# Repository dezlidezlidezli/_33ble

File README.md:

# _33BLE
A bluetooth drop-in PCB for the [_33 keyboard](https://github.com/tominabox1/_33-Keyboard) by [tominabox1](https://github.com/tominabox1). Documentation is available [here](https://dez.li/_33ble), and the ZMK config repository is available [here](https://github.com/dezlidezlidezli/underscore33-zmk-config). 

The board can be produced at [JLCPCB](jlcpcb.com) for rather cheap, and through their PCBA service they will assemble every component other than the the [Holyiot 18010 module](https://www.aliexpress.com/item/32868002366.html). You'll need to purchase this seperately, and solder it. Files for this can be found in the Production Files directory, when ordering make sure to choose "assemble bottom side" and tooling holes aded by JLCPCB. 

You'll also need to flash the bootloader to the Holyiot module. The bootloader file can be found [here](/underscore33_bootloader.hex), and should be flashed using an ST-Link V2 clone, or a J-Link. Details for how to do this are available on the nice!keyboards wiki, and on the nRFMicro wiki. Please note that the Holyiot module does not need to be unlocked. 

Alternatively, you can choose to export files suited for another manufacturer, such as Elecrow or PCBWay, where they will assemble the entire board. Some manufacturers may also be able to flash the bootloader in their factory, so this may be worth asking your customer support representative. 

Thank you to [Makenova](https://github.com/makenova) and [Matthew Dias](https://github.com/matthewdias) for funding the open-sourcing of this project.

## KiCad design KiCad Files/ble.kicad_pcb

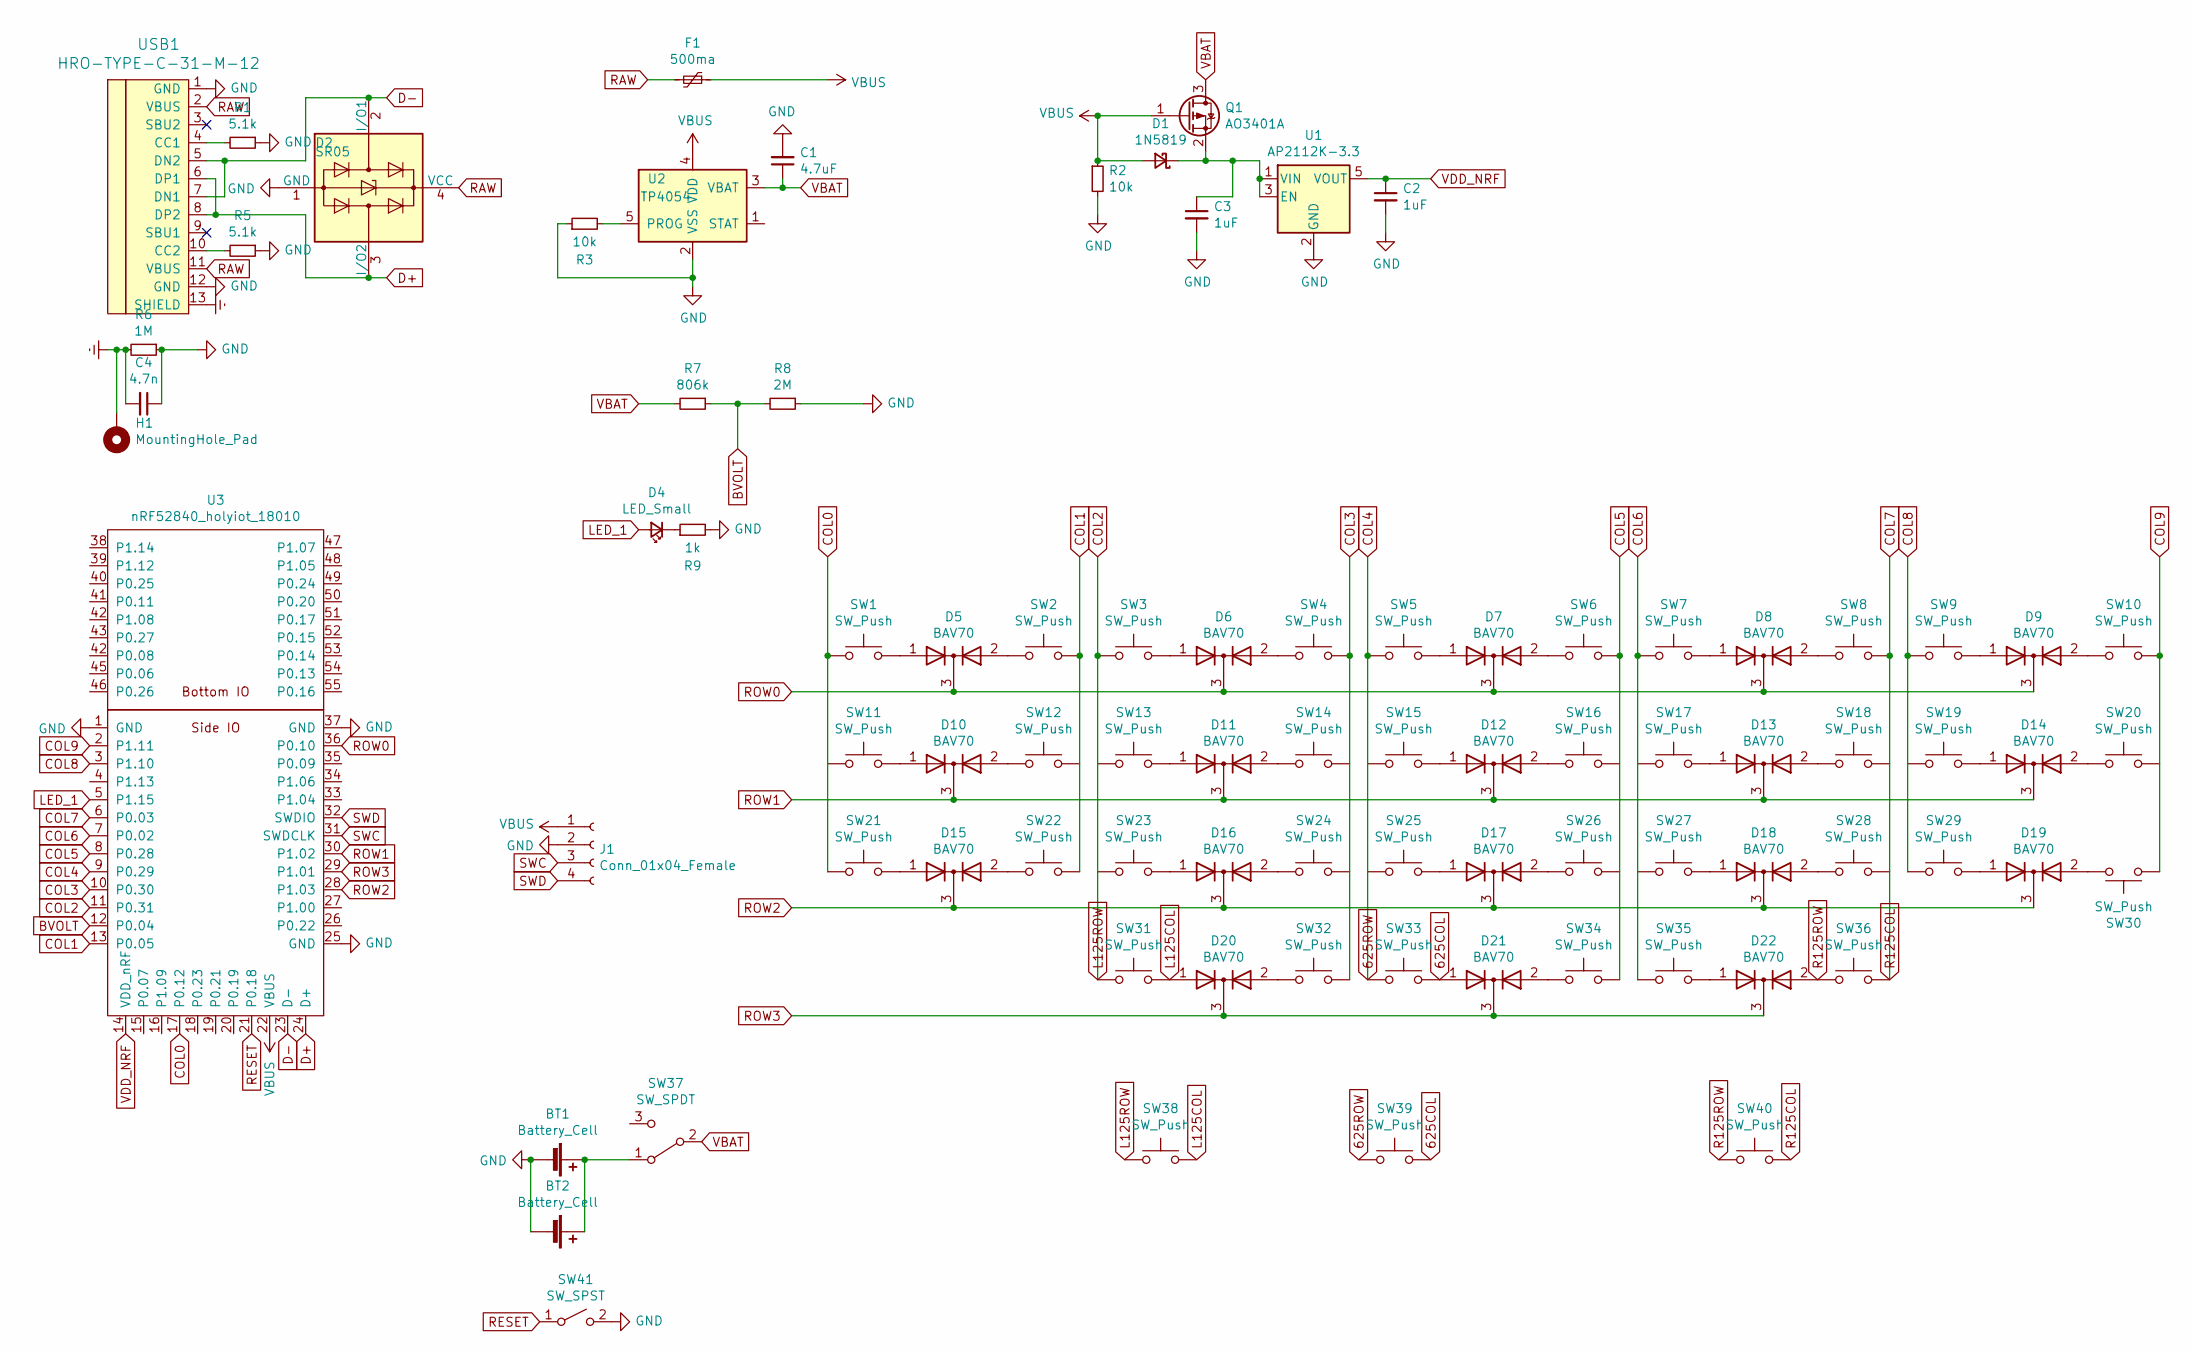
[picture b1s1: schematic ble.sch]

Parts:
BT1: Battery_Cell; JST_PH_S2B-PH-K_1x02_P2.00mm_Horizontal
BT2: Battery_Cell; custombatteryconnector
C1: 4.7uF; C_0805_2012Metric
C2, C3: 1uF; C_0805_2012Metric
C4: 4.7n; C_0805_2012Metric
D1: 1N5819; D_SOD-123
D2: SR05; SOT-143
D4: LED_Small; D_0805_2012Metric
D5, D6, D7, D8, D9, D10, D11, D12, D13, D14, D15, D16, D17, D18, D19, D20, D21, D22: BAV70; SOT-23
F1: 500ma; Fuse_1206_3216Metric
H1: MountingHole_Pad
J1: Conn_01x04_Female; PinSocket_1x04_P2.54mm_Vertical
Q1: AO3401A; SOT-23
R1, R5: 5.1k; R_0805_2012Metric
R2, R3: 10k; R_0805_2012Metric
R6: 1M; R_0805_2012Metric
R7: 806k; R_0805_2012Metric
R8: 2M; R_0805_2012Metric
R9: 1k; R_0805_2012Metric
SW1, SW2, SW3, SW4, SW5, SW6, SW7, SW8, SW9, SW10, SW11, SW12, SW13, SW14, SW15, SW16, SW17, SW18, SW19, SW20, SW21, SW22, SW23, SW24, SW25, SW26, SW27, SW28, SW29, SW30, SW31, SW36: SW_Push; MXOnly-1U-NoLED
SW32, SW35, SW38, SW40: SW_Push; MXOnly-1.25U-NoLED
SW33: SW_Push; MXOnly-2.25U-ReversedStabilizers-NoLED
SW34: SW_Push; MXOnly-2U-ReversedStabilizers-NoLED
SW37: SW_SPDT; SW_SPDT_PCM12
SW39: SW_Push; MXOnly-6.25U-ReversedStabilizers-NoLED
SW41: SW_SPST; SW_SPST_TL3342
U1: AP2112K-3.3; SOT-23-5
U2: TP4054; SOT-23-5
U3: nRF52840_holyiot_18010
USB1: HRO-TYPE-C-31-M-12; HRO-TYPE-C-31-M-12-HandSoldering

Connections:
625COL: D21.1 (A), SW33.2, SW39.2
625ROW: SW5.1, SW15.1, SW25.1, SW33.1, SW39.1, U3.9 (P0.29)
BVOLT: R7.1, R8.2, U3.12 (P0.04)
COL0: SW1.1, SW11.1, SW21.1, U3.17 (P0.12)
COL1: SW2.2, SW12.2, SW22.2, U3.13 (P0.05)
COL2: SW3.1, SW13.1, SW23.1, SW31.1, SW38.1, U3.11 (P0.31)
COL3: SW4.2, SW14.2, SW24.2, SW32.2, U3.10 (P0.30)
COL5: SW6.2, SW16.2, SW26.2, SW34.2, U3.8 (P0.28)
COL6: SW7.1, SW17.1, SW27.1, SW35.1, U3.7 (P0.02)
COL7: SW8.2, SW18.2, SW28.2, SW36.2, SW40.2, U3.6 (P0.03)
COL8: SW9.1, SW19.1, SW29.1, U3.3 (P1.10)
COL9: SW10.2, SW20.2, SW30.1, U3.2 (P1.11)
D+: D2.3 (I/O2), U3.24 (D+), USB1.6 (DP1), USB1.8 (DP2)
D-: D2.2 (I/O1), U3.23 (D-), USB1.5 (DN2), USB1.7 (DN1)
Earth: C4.2, H1.1, R6.2, USB1.13 (SHIELD)
GND: BT1.2 (-), BT2.2 (-), C1.2, C2.2, C3.2, C4.1, D2.1 (GND), J1.2, R1.1, R2.2, R3.1, R5.1, R6.1, R8.1, R9.2, SW41.2 (B), U1.2 (GND), U2.2 (VSS), U3.1 (GND), U3.25 (GND), U3.37 (GND), USB1.1 (GND), USB1.12 (GND)
L125COL: D20.1 (A), SW31.2, SW38.2
LED_1: D4.2 (A), U3.5 (P1.15)
unnamed: BT1.1 (+), BT2.1 (+), SW37.1 (A)
unnamed: C3.1, D1.1 (K), Q1.2 (S), U1.1 (VIN), U1.3 (EN)
unnamed: D4.1 (K), R9.1
unnamed: D5.1 (A), SW1.2
unnamed: D5.2 (A), SW2.1
unnamed: D6.1 (A), SW3.2
unnamed: D6.2 (A), SW4.1
unnamed: D7.1 (A), SW5.2
unnamed: D7.2 (A), SW6.1
unnamed: D8.1 (A), SW7.2
unnamed: D8.2 (A), SW8.1
unnamed: D9.1 (A), SW9.2
unnamed: D9.2 (A), SW10.1
unnamed: D10.1 (A), SW11.2
unnamed: D10.2 (A), SW12.1
unnamed: D11.1 (A), SW13.2
unnamed: D11.2 (A), SW14.1
unnamed: D12.1 (A), SW15.2
unnamed: D12.2 (A), SW16.1
unnamed: D13.1 (A), SW17.2
unnamed: D13.2 (A), SW18.1
unnamed: D14.1 (A), SW19.2
unnamed: D14.2 (A), SW20.1
unnamed: D15.1 (A), SW21.2
unnamed: D15.2 (A), SW22.1
unnamed: D16.1 (A), SW23.2
unnamed: D16.2 (A), SW24.1
unnamed: D17.1 (A), SW25.2
unnamed: D17.2 (A), SW26.1
unnamed: D18.1 (A), SW27.2
unnamed: D18.2 (A), SW28.1
unnamed: D19.1 (A), SW29.2
unnamed: D19.2 (A), SW30.2
unnamed: D20.2 (A), SW32.1
unnamed: D21.2 (A), SW34.1
unnamed: D22.1 (A), SW35.2
unnamed: R1.2, USB1.4 (CC1)
unnamed: R3.2, U2.5 (PROG)
unnamed: R5.2, USB1.10 (CC2)
R125ROW: D22.2 (A), SW36.1, SW40.1
RAW: D2.4 (VCC), F1.2, USB1.2 (VBUS), USB1.11 (VBUS)
RESET: SW41.1 (A), U3.21 (P0.18)
ROW0: D5.3 (K), D6.3 (K), D7.3 (K), D8.3 (K), D9.3 (K), U3.36 (P0.10)
ROW1: D10.3 (K), D11.3 (K), D12.3 (K), D13.3 (K), D14.3 (K), U3.30 (P1.02)
ROW2: D15.3 (K), D16.3 (K), D17.3 (K), D18.3 (K), D19.3 (K), U3.28 (P1.03)
ROW3: D20.3 (K), D21.3 (K), D22.3 (K), U3.29 (P1.01)
SWC: J1.3, U3.31 (SWDCLK)
SWD: J1.4, U3.32 (SWDIO)
VBAT: C1.1, Q1.3 (D), R7.2, SW37.2 (B), U2.3 (VBAT)
VBUS: D1.2 (A), F1.1, J1.1, Q1.1 (G), R2.1, U2.4 (VDD), U3.22 (VBUS)
VDD_NRF: C2.1, U1.5 (VOUT), U3.14 (VDD_nRF)

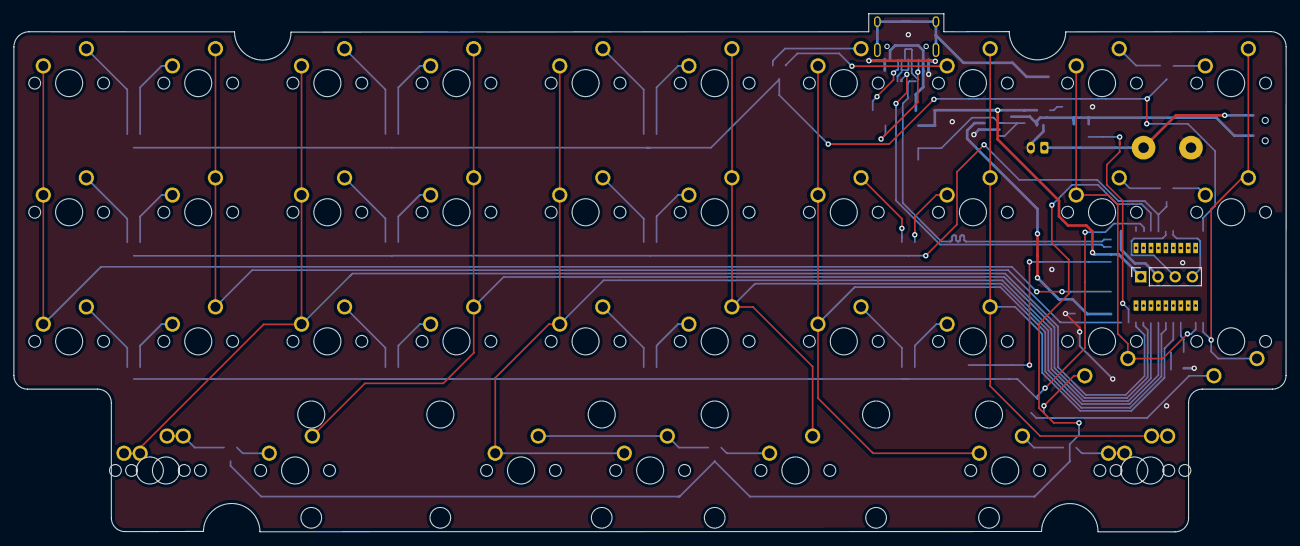
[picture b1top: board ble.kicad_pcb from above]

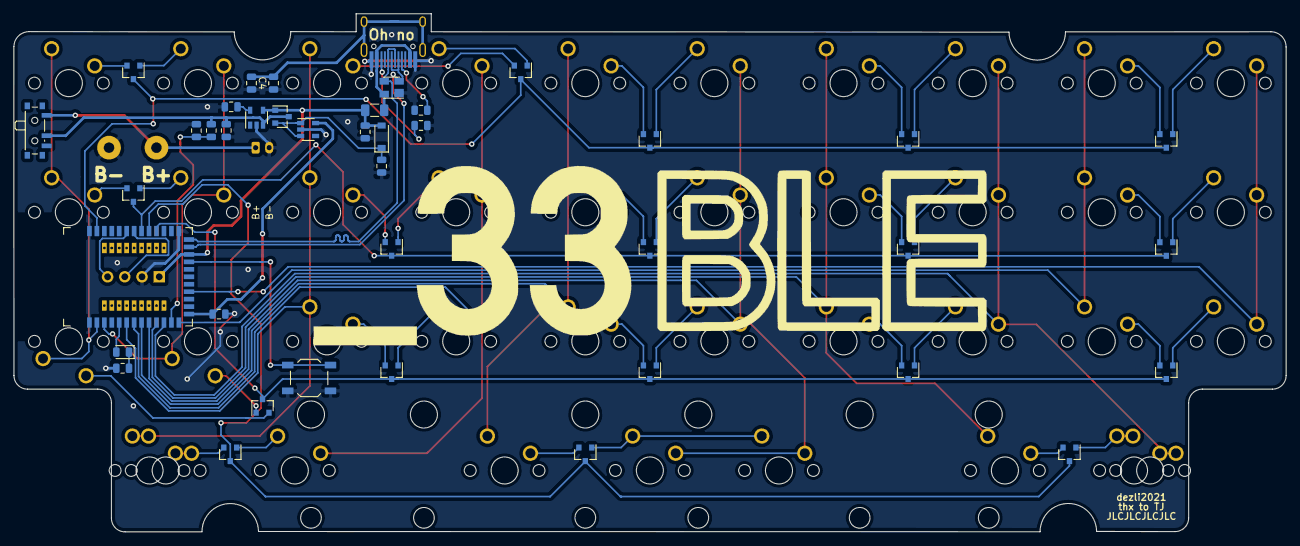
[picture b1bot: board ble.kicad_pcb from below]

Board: 2 copper layers, 187.7 x 76.4 mm, 83 parts (43 on the bottom side), 69 nets.

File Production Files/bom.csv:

Comment,Designator,Footprint,LCSC Part #（optional）,,,
SW_SPST,SW41,SW-SMD-4_5.2x5.2x3.7P,C92584,,,
SR05,D2,SOT-143,C384891,,,
BAV70,"D8,D22,D21,D20,D19,D18,D17,D16,D15,D14,D13,D12,D11,D10,D9,D7,D6,D5",SOT-23,C68978,,,
4.7n,C4,C_0805_2012Metric,C1744,,,
SW_SPDT,SW37,SMD-7PIN,C109335,,,
HRO-TYPE-C-31-M-12,USB1,TYPE-C-31_L8.94_W7.3,C165948,,,
TP4054,U2,SOT-23-5,C32574,,,
AP2112K-3.3,U1,SOT-23-5,C51118,,,
1k,R9,R_0805_2012Metric,C17513,,,
2M,R8,R_0805_2012Metric,C26112,,,
806k,R7,R_0805_2012Metric,C63494,,,
1M,R6,R_0805_2012Metric,C17514,,,
5.1k,"R5,R1",R_0805_2012Metric,C27834,,,
10k,"R3,R2",R_0805_2012Metric,C17414,,,
AO3401A,Q1,SOT-23,C306862,,,
500ma,F1,Fuse_1206_3216Metric,C70076,,,
LED_Small,D4,D_0805_2012Metric,C2296,,,
1N5819,D1,D_SOD-123,C169540,,,
1uF,"C3,C2",C_0805_2012Metric,C28323,,,
4.7uF,C1,C_0805_2012Metric,C1779,,,
Battery_Cell,BT1,CONN-TH_A2001WR-2P,C225207,,,

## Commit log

2021-07-03 commit the actual files
2022-06-19 updated bootloader
